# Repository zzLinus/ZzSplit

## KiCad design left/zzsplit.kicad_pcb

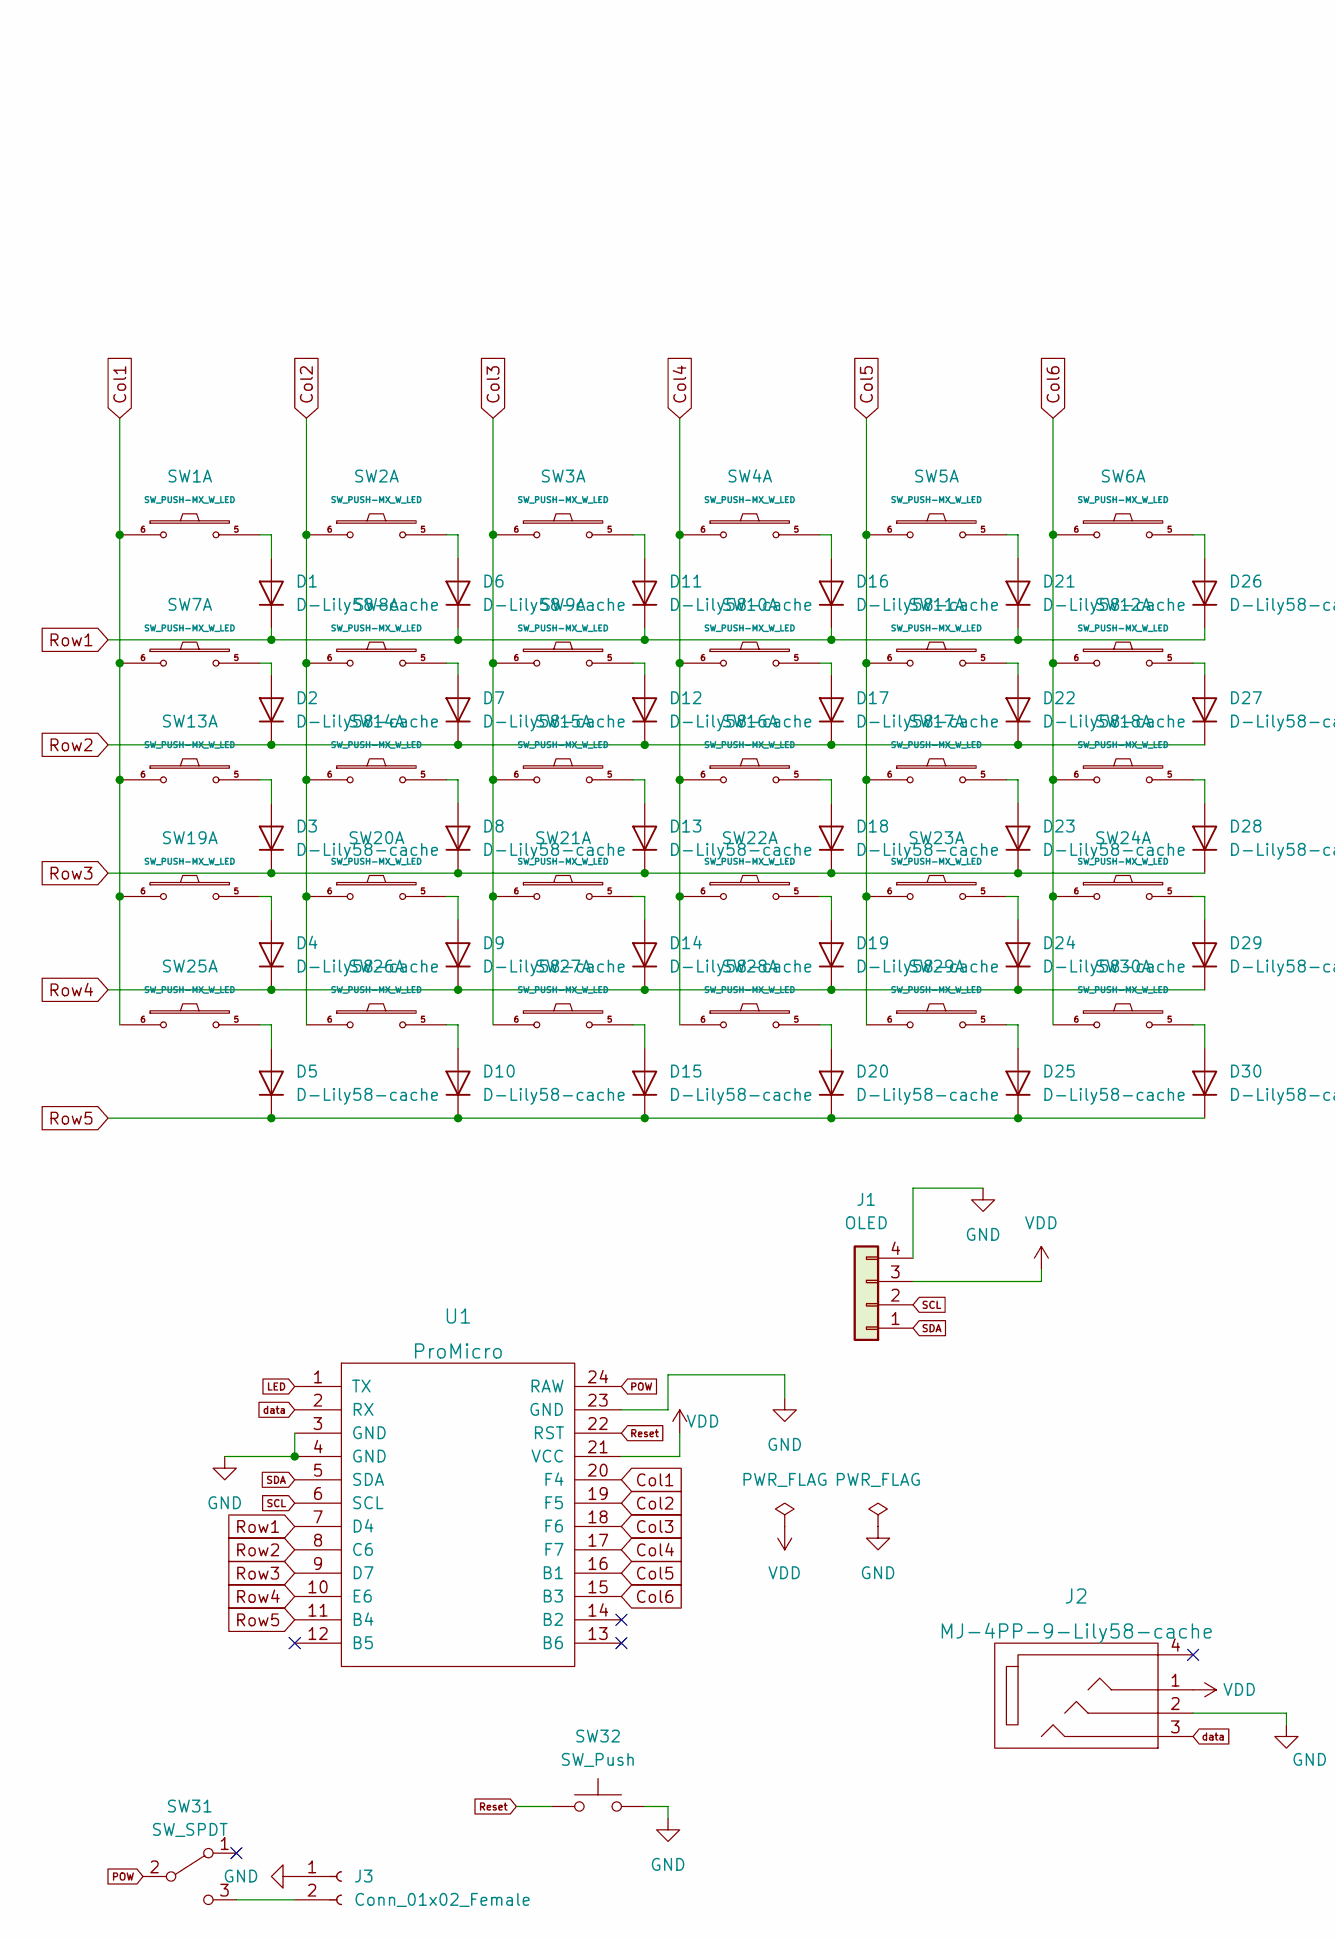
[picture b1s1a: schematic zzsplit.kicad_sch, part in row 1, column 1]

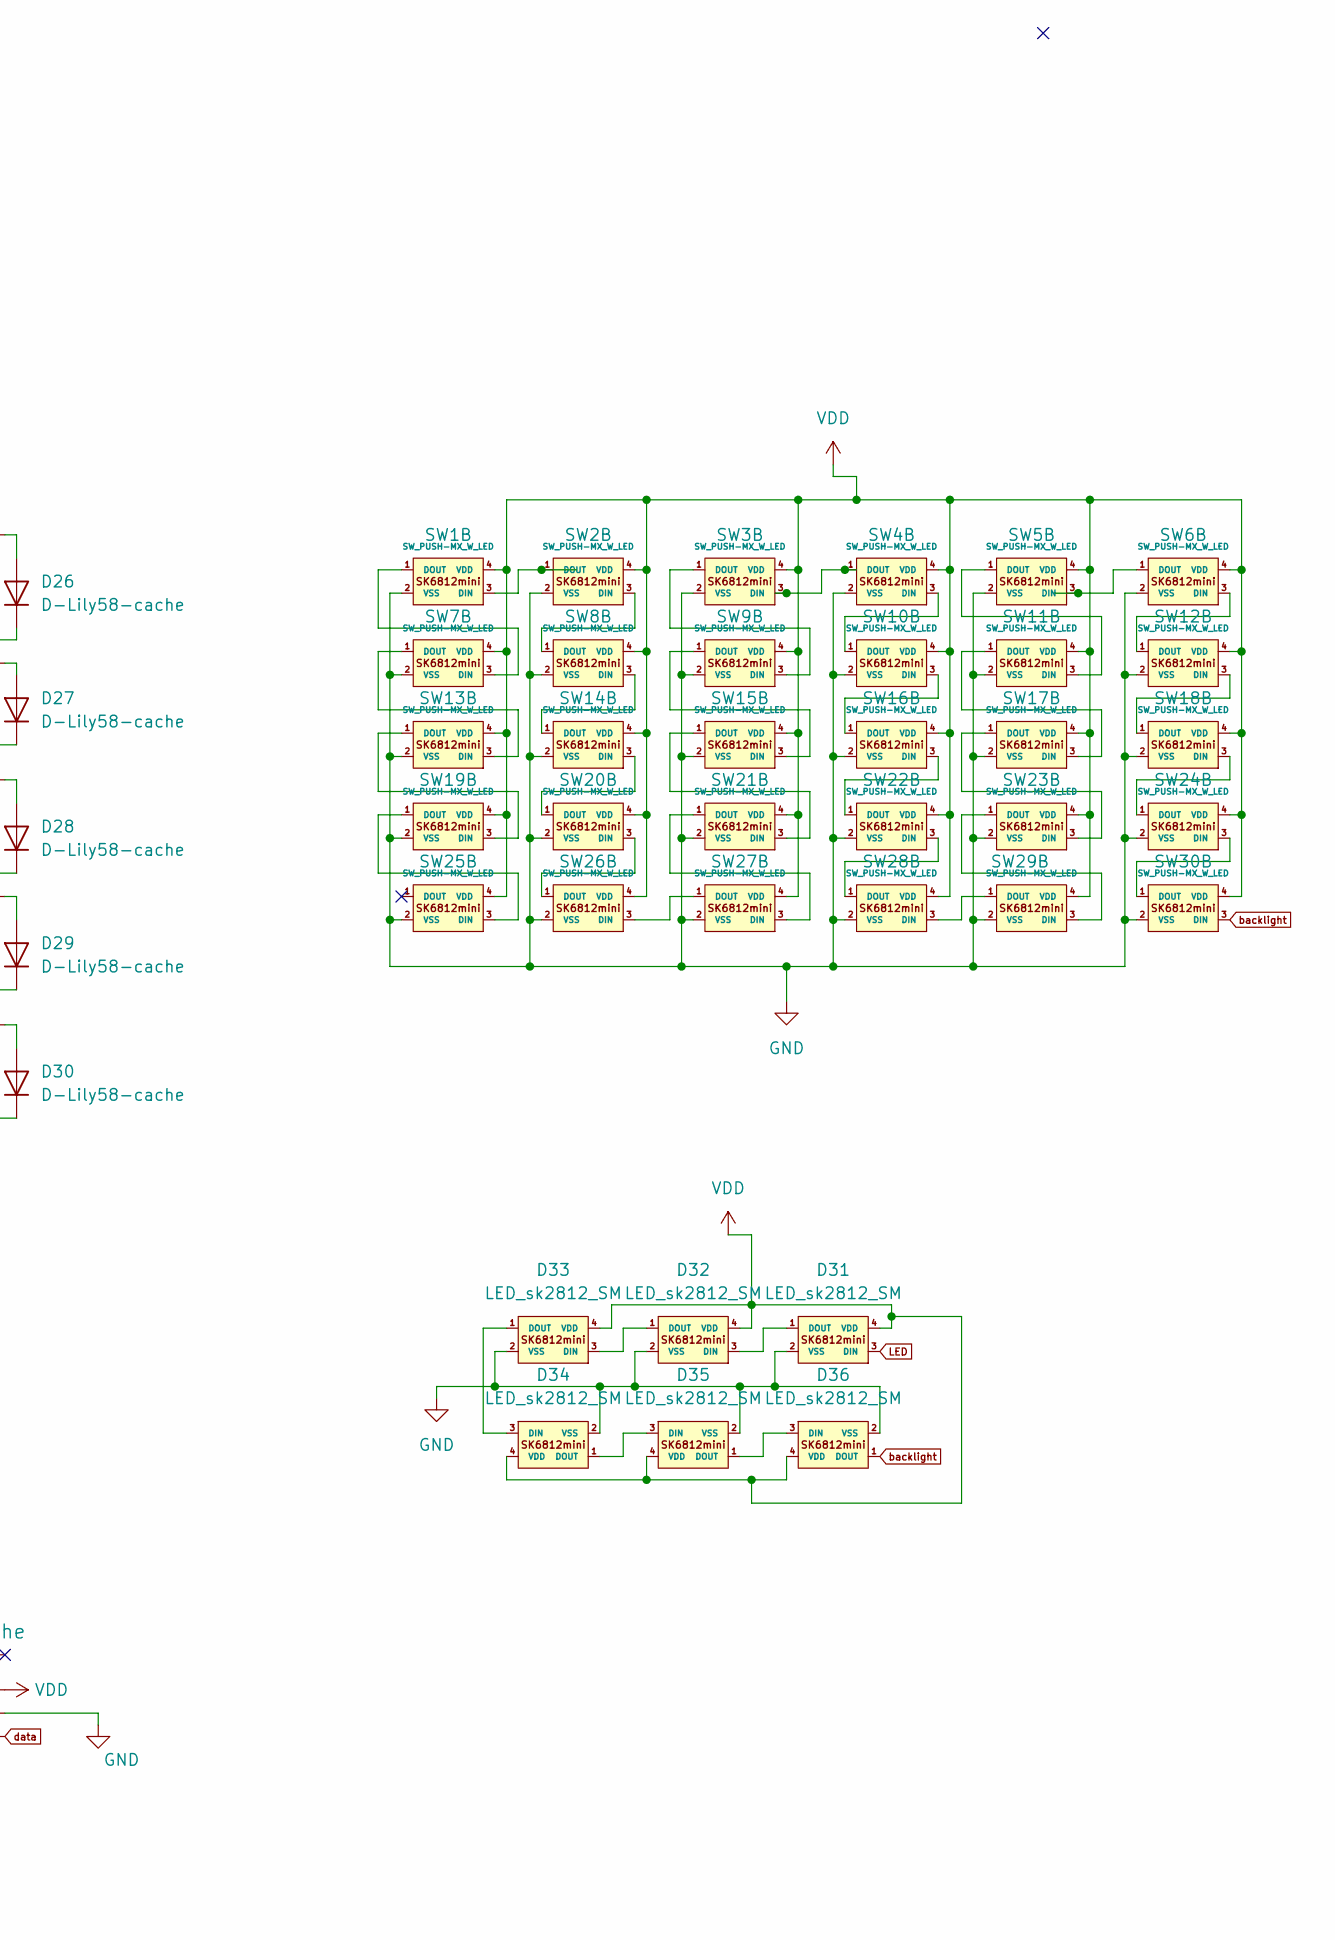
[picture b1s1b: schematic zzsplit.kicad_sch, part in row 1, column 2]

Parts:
D1, D2, D3, D4, D5, D6, D7, D8, D9, D10, D11, D12, D13, D14, D15, D16, D17, D18, D19, D20, D21, D22, D23, D24, D25, D26, D27, D28, D29, D30: D-Lily58-cache; crkbd-diode
D31, D32, D33, D34, D35, D36: LED_sk2812_SM; SK6812MINI_underglow_dev
J1: OLED; OLED_4Pin
J2: MJ-4PP-9-Lily58-cache; MJ-4PP-9
J3: Conn_01x02_Female; SolderWire-0.1sqmm_1x02_P3.6mm_D0.4mm_OD1mm
SW1, SW2, SW3, SW4, SW5, SW6, SW7, SW8, SW9, SW10, SW11, SW12, SW13, SW14, SW15, SW16, SW17, SW18, SW19, SW20, SW21, SW22, SW23, SW24, SW25, SW26, SW27, SW28, SW29, SW30: SW_PUSH-MX_W_LED; SK6812MINI_and_cherry
SW31: SW_SPDT; switch-MSK-12C02-smd
SW32: SW_Push; TACT_SWITCH_TVBP06
U1: ProMicro; ArduinoProMicro

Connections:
Col1: SW1.6, SW7.6, SW13.6, SW19.6, SW25.6, U1.20 (F4)
Col2: SW2.6, SW8.6, SW14.6, SW20.6, SW26.6, U1.19 (F5)
Col3: SW3.6, SW9.6, SW15.6, SW21.6, SW27.6, U1.18 (F6)
Col4: SW4.6, SW10.6, SW16.6, SW22.6, SW28.6, U1.17 (F7)
Col5: SW5.6, SW11.6, SW17.6, SW23.6, SW29.6, U1.16 (B1)
Col6: SW6.6, SW12.6, SW18.6, SW24.6, SW30.6, U1.15 (B3)
GND: D31.2 (VSS), D32.2 (VSS), D33.2 (VSS), D34.2 (VSS), D35.2 (VSS), D36.2 (VSS), J1.4, J2.2, J3.1, SW1.2 (VSS), SW2.2 (VSS), SW3.2 (VSS), SW4.2 (VSS), SW5.2 (VSS), SW6.2 (VSS), SW7.2 (VSS), SW8.2 (VSS), SW9.2 (VSS), SW10.2 (VSS), SW11.2 (VSS), SW12.2 (VSS), SW13.2 (VSS), SW14.2 (VSS), SW15.2 (VSS), SW16.2 (VSS), SW17.2 (VSS), SW18.2 (VSS), SW19.2 (VSS), SW20.2 (VSS), SW21.2 (VSS), SW22.2 (VSS), SW23.2 (VSS), SW24.2 (VSS), SW25.2 (VSS), SW26.2 (VSS), SW27.2 (VSS), SW28.2 (VSS), SW29.2 (VSS), SW30.2 (VSS), SW32.2, U1.3 (GND), U1.4 (GND), U1.23 (GND)
LED: D31.3 (DIN), U1.1 (TX)
unnamed: D1.2 (A), SW1.5
unnamed: D2.2 (A), SW7.5
unnamed: D3.2 (A), SW13.5
unnamed: D4.2 (A), SW19.5
unnamed: D5.2 (A), SW25.5
unnamed: D6.2 (A), SW2.5
unnamed: D7.2 (A), SW8.5
unnamed: D8.2 (A), SW14.5
unnamed: D9.2 (A), SW20.5
unnamed: D10.2 (A), SW26.5
unnamed: D11.2 (A), SW3.5
unnamed: D12.2 (A), SW9.5
unnamed: D13.2 (A), SW15.5
unnamed: D14.2 (A), SW21.5
unnamed: D15.2 (A), SW27.5
unnamed: D16.2 (A), SW4.5
unnamed: D17.2 (A), SW10.5
unnamed: D18.2 (A), SW16.5
unnamed: D19.2 (A), SW22.5
unnamed: D20.2 (A), SW28.5
unnamed: D21.2 (A), SW5.5
unnamed: D22.2 (A), SW11.5
unnamed: D23.2 (A), SW17.5
unnamed: D24.2 (A), SW23.5
unnamed: D25.2 (A), SW29.5
unnamed: D26.2 (A), SW6.5
unnamed: D27.2 (A), SW12.5
unnamed: D28.2 (A), SW18.5
unnamed: D29.2 (A), SW24.5
unnamed: D30.2 (A), SW30.5
unnamed: D31.1 (DOUT), D32.3 (DIN)
unnamed: D32.1 (DOUT), D33.3 (DIN)
unnamed: D33.1 (DOUT), D34.3 (DIN)
unnamed: D34.1 (DOUT), D35.3 (DIN)
unnamed: D35.1 (DOUT), D36.3 (DIN)
unnamed: J3.2, SW31.3 (C)
unnamed: SW1.1 (DOUT), SW7.3 (DIN)
unnamed: SW1.3 (DIN), SW2.1 (DOUT)
unnamed: SW2.3 (DIN), SW8.1 (DOUT)
unnamed: SW3.1 (DOUT), SW9.3 (DIN)
unnamed: SW3.3 (DIN), SW4.1 (DOUT)
unnamed: SW5.3 (DIN), SW6.1 (DOUT)
unnamed: SW4.3 (DIN), SW10.1 (DOUT)
unnamed: SW10.3 (DIN), SW16.1 (DOUT)
unnamed: SW11.1 (DOUT), SW17.3 (DIN)
unnamed: SW5.1 (DOUT), SW11.3 (DIN)
unnamed: SW6.3 (DIN), SW12.1 (DOUT)
unnamed: SW12.3 (DIN), SW18.1 (DOUT)
unnamed: SW13.1 (DOUT), SW19.3 (DIN)
unnamed: SW7.1 (DOUT), SW13.3 (DIN)
unnamed: SW8.3 (DIN), SW14.1 (DOUT)
unnamed: SW14.3 (DIN), SW20.1 (DOUT)
unnamed: SW15.1 (DOUT), SW21.3 (DIN)
unnamed: SW9.1 (DOUT), SW15.3 (DIN)
unnamed: SW16.3 (DIN), SW22.1 (DOUT)
unnamed: SW17.1 (DOUT), SW23.3 (DIN)
unnamed: SW18.3 (DIN), SW24.1 (DOUT)
unnamed: SW19.1 (DOUT), SW25.3 (DIN)
unnamed: SW20.3 (DIN), SW26.1 (DOUT)
unnamed: SW21.1 (DOUT), SW27.3 (DIN)
unnamed: SW22.3 (DIN), SW28.1 (DOUT)
unnamed: SW23.1 (DOUT), SW29.3 (DIN)
unnamed: SW24.3 (DIN), SW30.1 (DOUT)
unnamed: SW26.3 (DIN), SW27.1 (DOUT)
unnamed: SW28.3 (DIN), SW29.1 (DOUT)
POW: SW31.2 (B), U1.24 (RAW)
Reset: SW32.1, U1.22 (RST)
Row1: D1.1 (K), D6.1 (K), D11.1 (K), D16.1 (K), D21.1 (K), D26.1 (K), U1.7 (D4)
Row2: D2.1 (K), D7.1 (K), D12.1 (K), D17.1 (K), D22.1 (K), D27.1 (K), U1.8 (C6)
Row3: D3.1 (K), D8.1 (K), D13.1 (K), D18.1 (K), D23.1 (K), D28.1 (K), U1.9 (D7)
Row4: D4.1 (K), D9.1 (K), D14.1 (K), D19.1 (K), D24.1 (K), D29.1 (K), U1.10 (E6)
Row5: D5.1 (K), D10.1 (K), D15.1 (K), D20.1 (K), D25.1 (K), D30.1 (K), U1.11 (B4)
SCL: J1.2, U1.6 (SCL)
SDA: J1.1, U1.5 (SDA)
VDD: D31.4 (VDD), D32.4 (VDD), D33.4 (VDD), D34.4 (VDD), D35.4 (VDD), D36.4 (VDD), J1.3, J2.1, SW1.4 (VDD), SW2.4 (VDD), SW3.4 (VDD), SW4.4 (VDD), SW5.4 (VDD), SW6.4 (VDD), SW7.4 (VDD), SW8.4 (VDD), SW9.4 (VDD), SW10.4 (VDD), SW11.4 (VDD), SW12.4 (VDD), SW13.4 (VDD), SW14.4 (VDD), SW15.4 (VDD), SW16.4 (VDD), SW17.4 (VDD), SW18.4 (VDD), SW19.4 (VDD), SW20.4 (VDD), SW21.4 (VDD), SW22.4 (VDD), SW23.4 (VDD), SW24.4 (VDD), SW25.4 (VDD), SW26.4 (VDD), SW27.4 (VDD), SW28.4 (VDD), SW29.4 (VDD), SW30.4 (VDD), U1.21 (VCC)
backlight: D36.1 (DOUT), SW30.3 (DIN)
data: J2.3, U1.2 (RX)

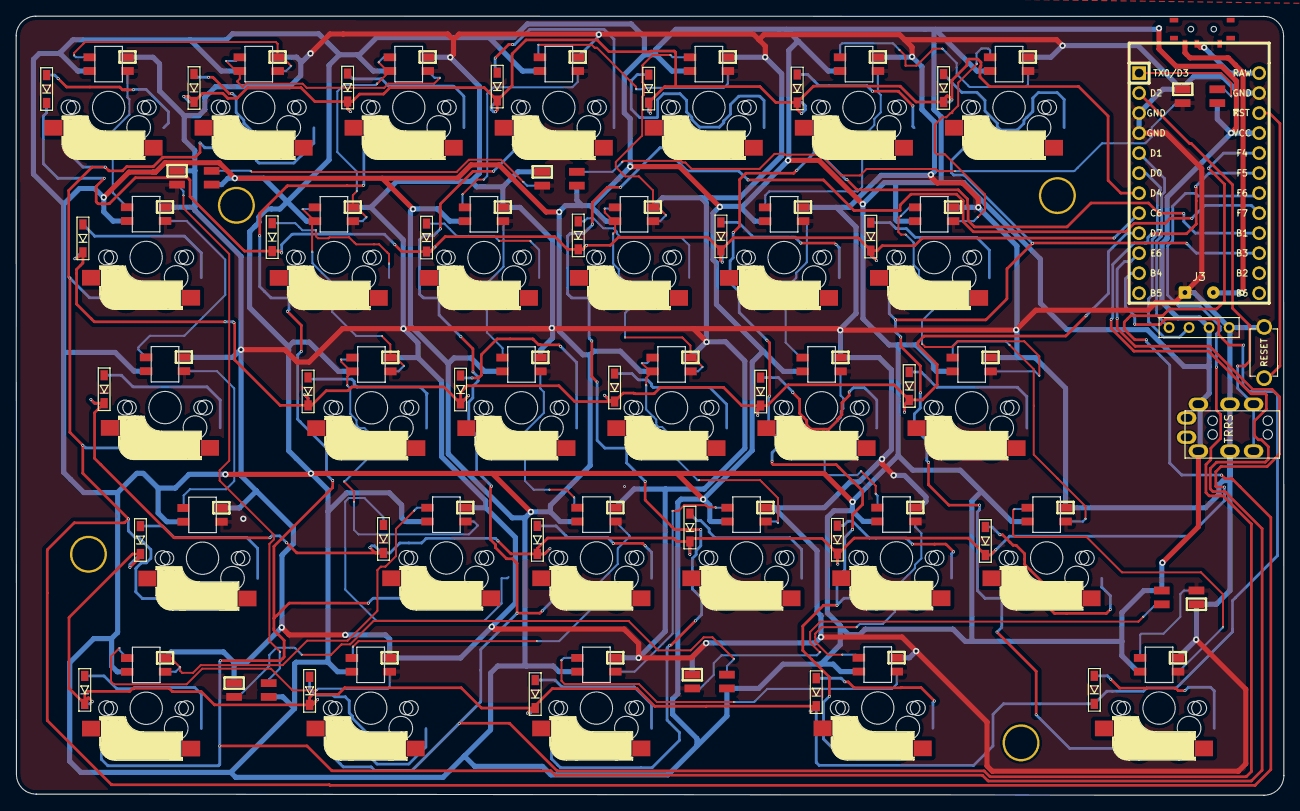
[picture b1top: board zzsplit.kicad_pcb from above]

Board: 2 copper layers, 160.9 x 98.8 mm, 73 parts (1 on the bottom side), 85 nets.

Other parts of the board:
.V1: LOGO; melogo

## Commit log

2022-08-01 first commit: left half
2022-08-02 right half
2022-08-03 gerber files for right and left pcbs
2022-08-03 holes
2022-08-07 new gerbers && component.md
2022-08-10 add the fucking stupid led cut edges and new gerbers
2022-08-10 pcb fixup && new gerber
2022-08-16 fix rgb powerline problem and new 3 pin 2 channel switches
2022-09-08 new top & bottom plates
